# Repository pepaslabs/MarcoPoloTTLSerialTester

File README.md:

# MarcoPoloTTLSerialTester
A board for testing a TTL Serial communication channel.

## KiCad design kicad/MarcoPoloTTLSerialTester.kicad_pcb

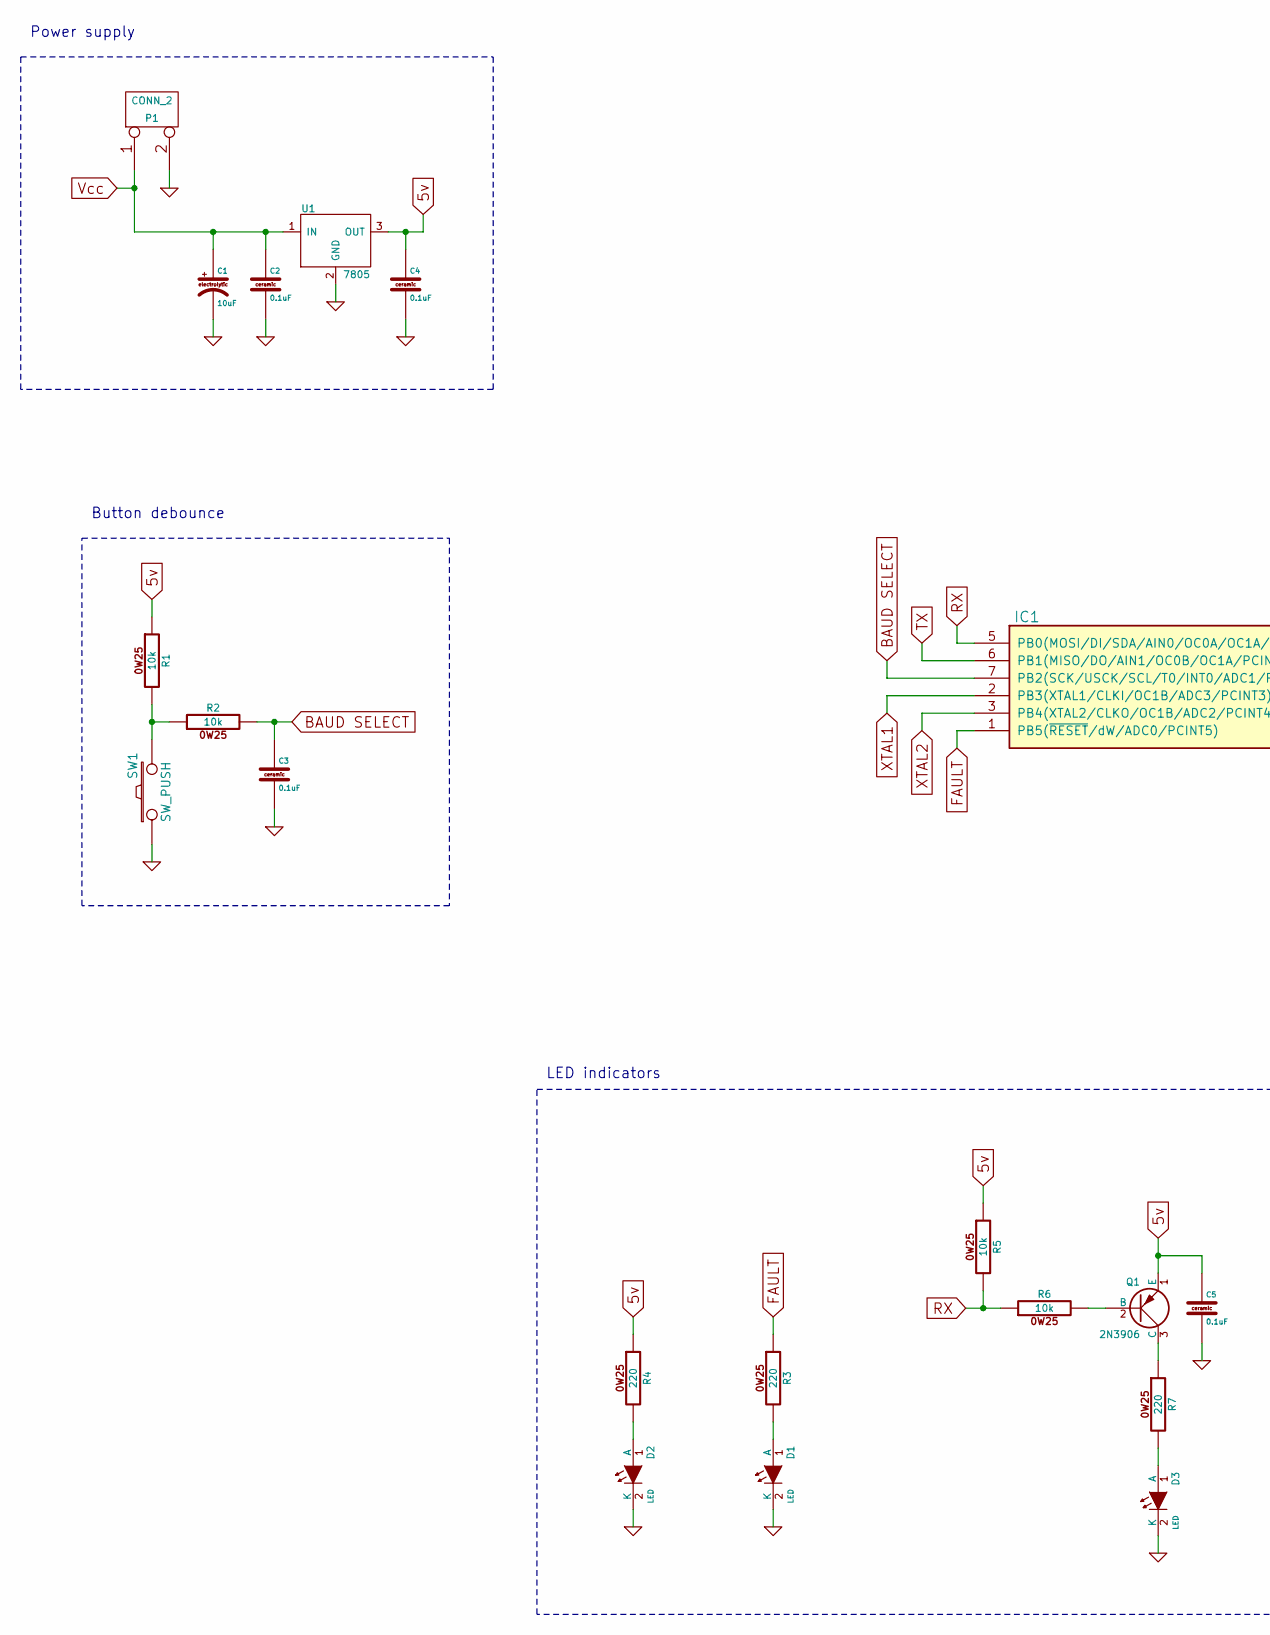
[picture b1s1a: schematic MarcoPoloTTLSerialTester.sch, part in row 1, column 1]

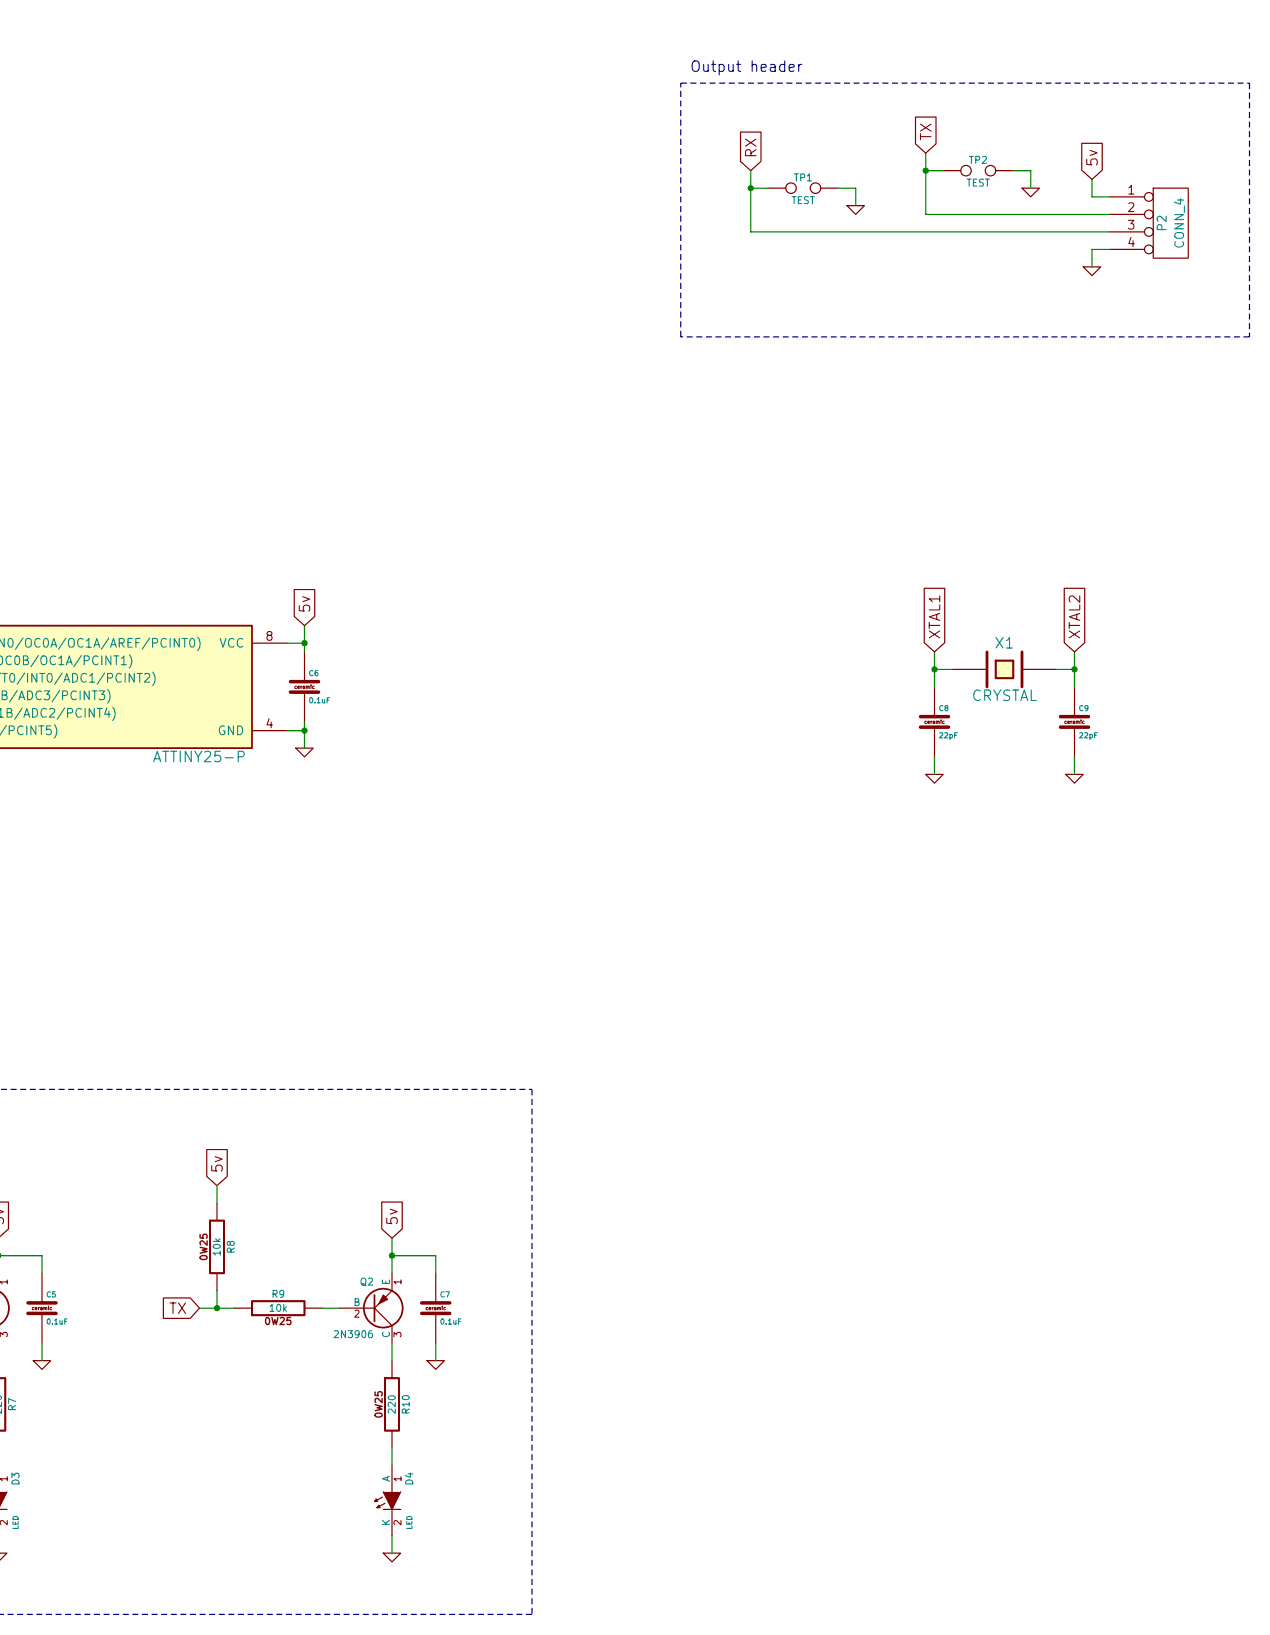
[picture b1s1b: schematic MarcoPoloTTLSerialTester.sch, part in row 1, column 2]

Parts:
C1: 10uF
C2, C3, C4, C5, C6, C7: 0.1uF
C8, C9: 22pF
D1, D2, D3, D4: LED
IC1: ATTINY25-P; DIP8
P1: CONN_2
P2: CONN_4
Q1, Q2: 2N3906
R1, R2, R5, R6, R8, R9: 10k
R3, R4, R7, R10: 220
SW1: SW_PUSH
TP1, TP2: TEST
U1: 7805
X1: CRYSTAL

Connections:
5v: C4.1, C5.1, C6.1, C7.1, IC1.8 (VCC), P2.1, Q1.1 (E), Q2.1 (E), R1.1, R4.1, R5.1, R8.1, U1.3 (OUT)
BAUD SELECT: C3.1, IC1.7 (PB2(SCK/USCK/SCL/T0/INT0/ADC1/PCINT2)), R2.2
FAULT: IC1.1 (PB5(~RESET~/dW/ADC0/PCINT5)), R3.1
GND: C1.2, C2.2, C3.2, C4.2, C5.2, C6.2, C7.2, C8.2, C9.2, D1.2 (K), D2.2 (K), D3.2 (K), D4.2 (K), IC1.4 (GND), P1.2 (PM), P2.4, SW1.1, TP1.2, TP2.2, U1.2 (GND)
unnamed: D1.1 (A), R3.2
unnamed: R1.2, R2.1, SW1.2
unnamed: Q1.2 (B), R6.2
unnamed: Q1.3 (C), R7.1
unnamed: D3.1 (A), R7.2
unnamed: D2.1 (A), R4.2
unnamed: Q2.2 (B), R9.2
unnamed: D4.1 (A), R10.2
unnamed: Q2.3 (C), R10.1
RX: IC1.5 (PB0(MOSI/DI/SDA/AIN0/OC0A/OC1A/AREF/PCI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), P2.3, R5.2, R6.1, TP1.1
TX: IC1.6 (PB1(MISO/DO/AIN1/OC0B/OC1A/PCINT1)), P2.2, R8.2, R9.1, TP2.1
Vcc: C1.1, C2.1, P1.1, U1.1 (IN)
XTAL1: C8.1, IC1.2 (PB3(XTAL1/CLKI/OC1B/ADC3/PCINT3)), X1.1
XTAL2: C9.1, IC1.3 (PB4(XTAL2/CLKO/OC1B/ADC2/PCINT4)), X1.2

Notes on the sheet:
LED indicators
Power supply
Button debounce
Output header

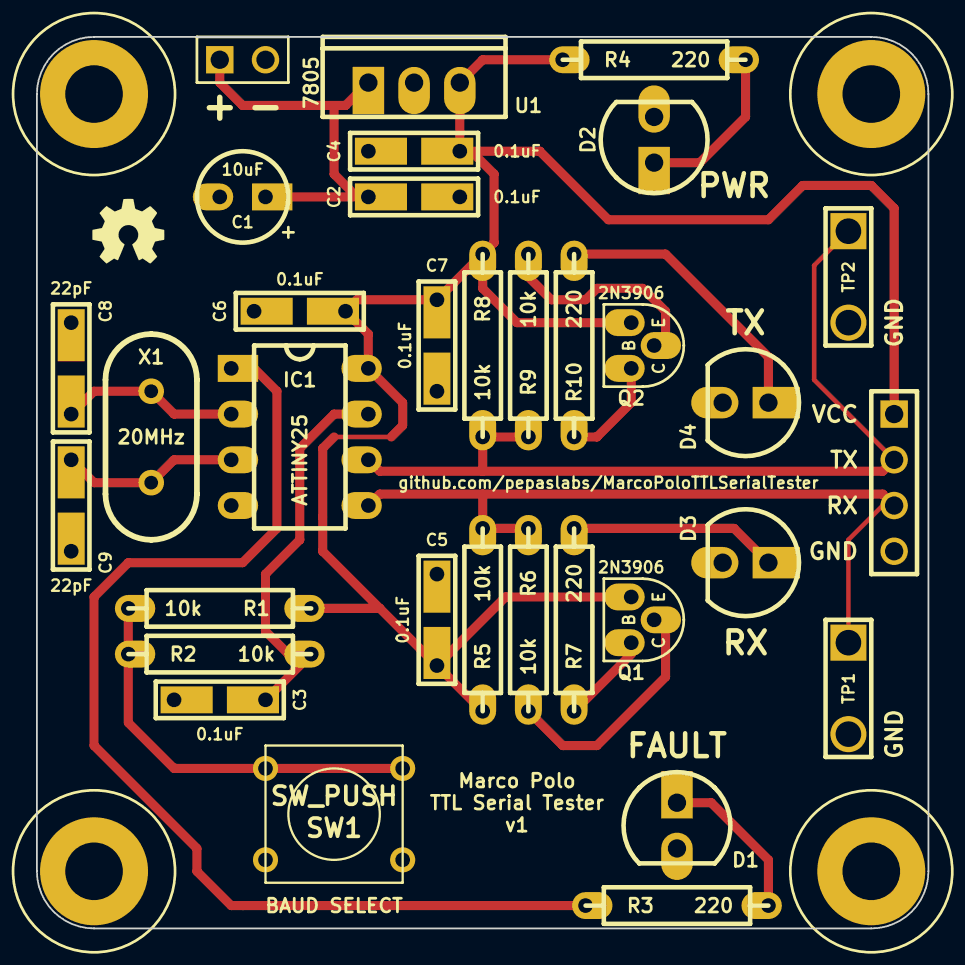
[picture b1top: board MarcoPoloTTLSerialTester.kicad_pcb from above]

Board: 2 copper layers, 49.5 x 49.5 mm, 37 parts (0 on the bottom side), 18 nets.

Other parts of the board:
H***: Val**; hole_M3
H***#2, H***#3, H***#4: Val**; hole_M3
